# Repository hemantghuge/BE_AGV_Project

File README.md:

# BE_AGV_Project 2019-2020

## Project Title
Smart and Efficient Techniques for Automated Guided Vehicle

## College
Government College of Engineering and Research, Avasari (Khurd)

## Department
Electronics and Telecommunication Engineering

#### Click below for viewing YouTube video.

## Mentor

**Name:** Dr. Kirti Vasant Thakur
**Email ID:** kirti79@gmail.com

## Members

**Roll No.**: 16131002 **Name:** Aadesh Rambhau Borate **Email ID:** aadeshborate5@gmail.com

**Roll No.:** 16131035 **Name:** Hemant Goraksh Ghuge **Email ID:** hemantgghuge@gmail.com

**Roll No.:** 16131052 **Name:** Unnati Raju Kulkarni **Email ID:** unnatikulkarni46@gmail.com

**Roll No.:** 17231025 **Name:** Revati Anand Kulkarni **Email ID:** kulkarnirevati988@gmail.com

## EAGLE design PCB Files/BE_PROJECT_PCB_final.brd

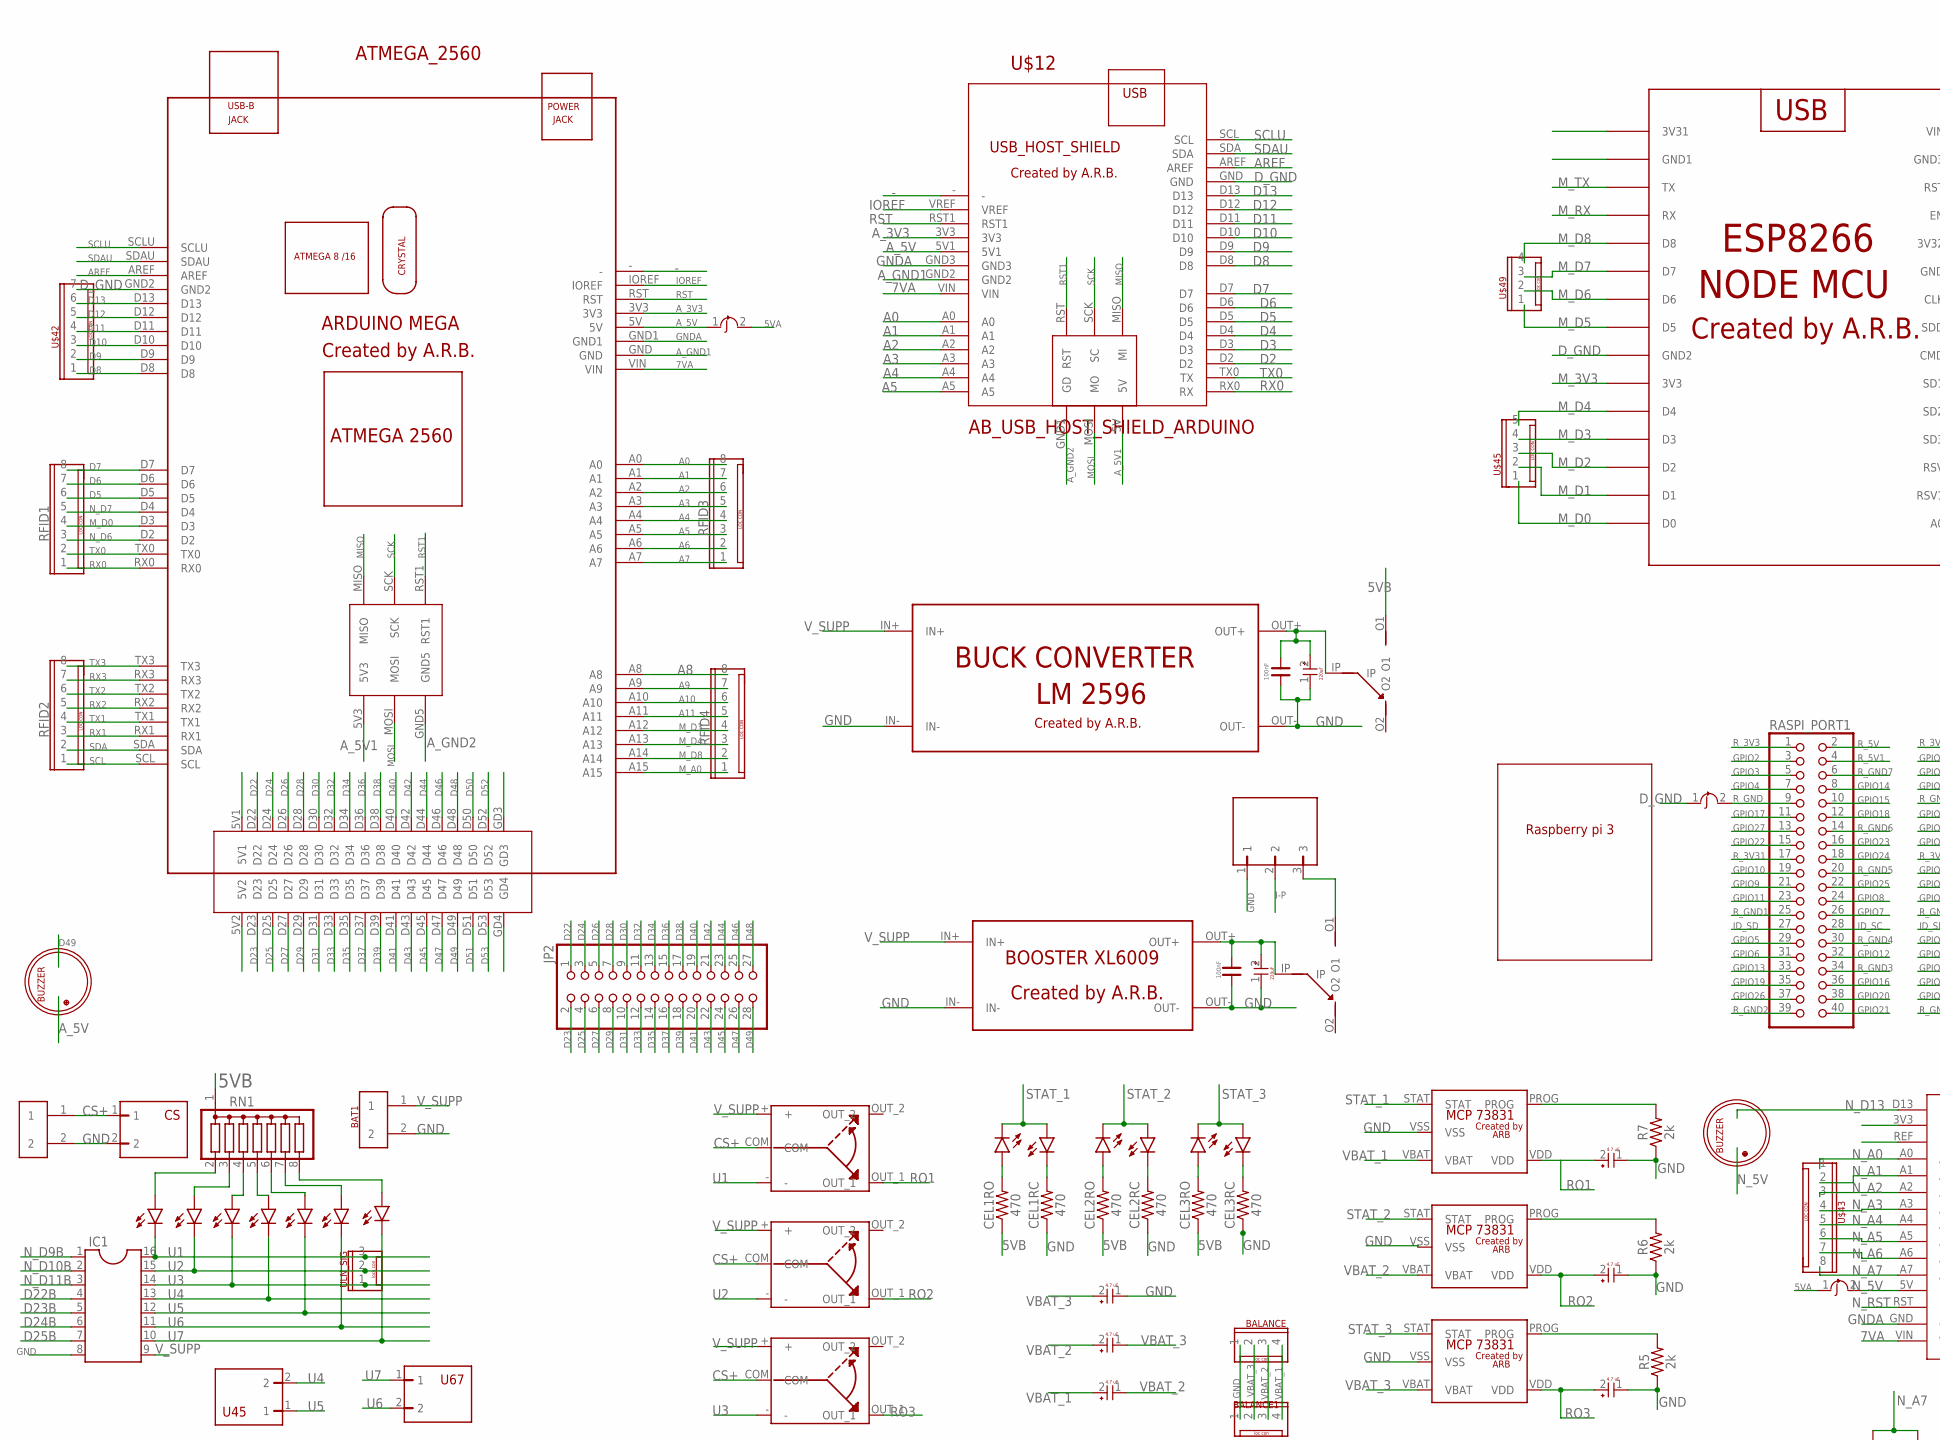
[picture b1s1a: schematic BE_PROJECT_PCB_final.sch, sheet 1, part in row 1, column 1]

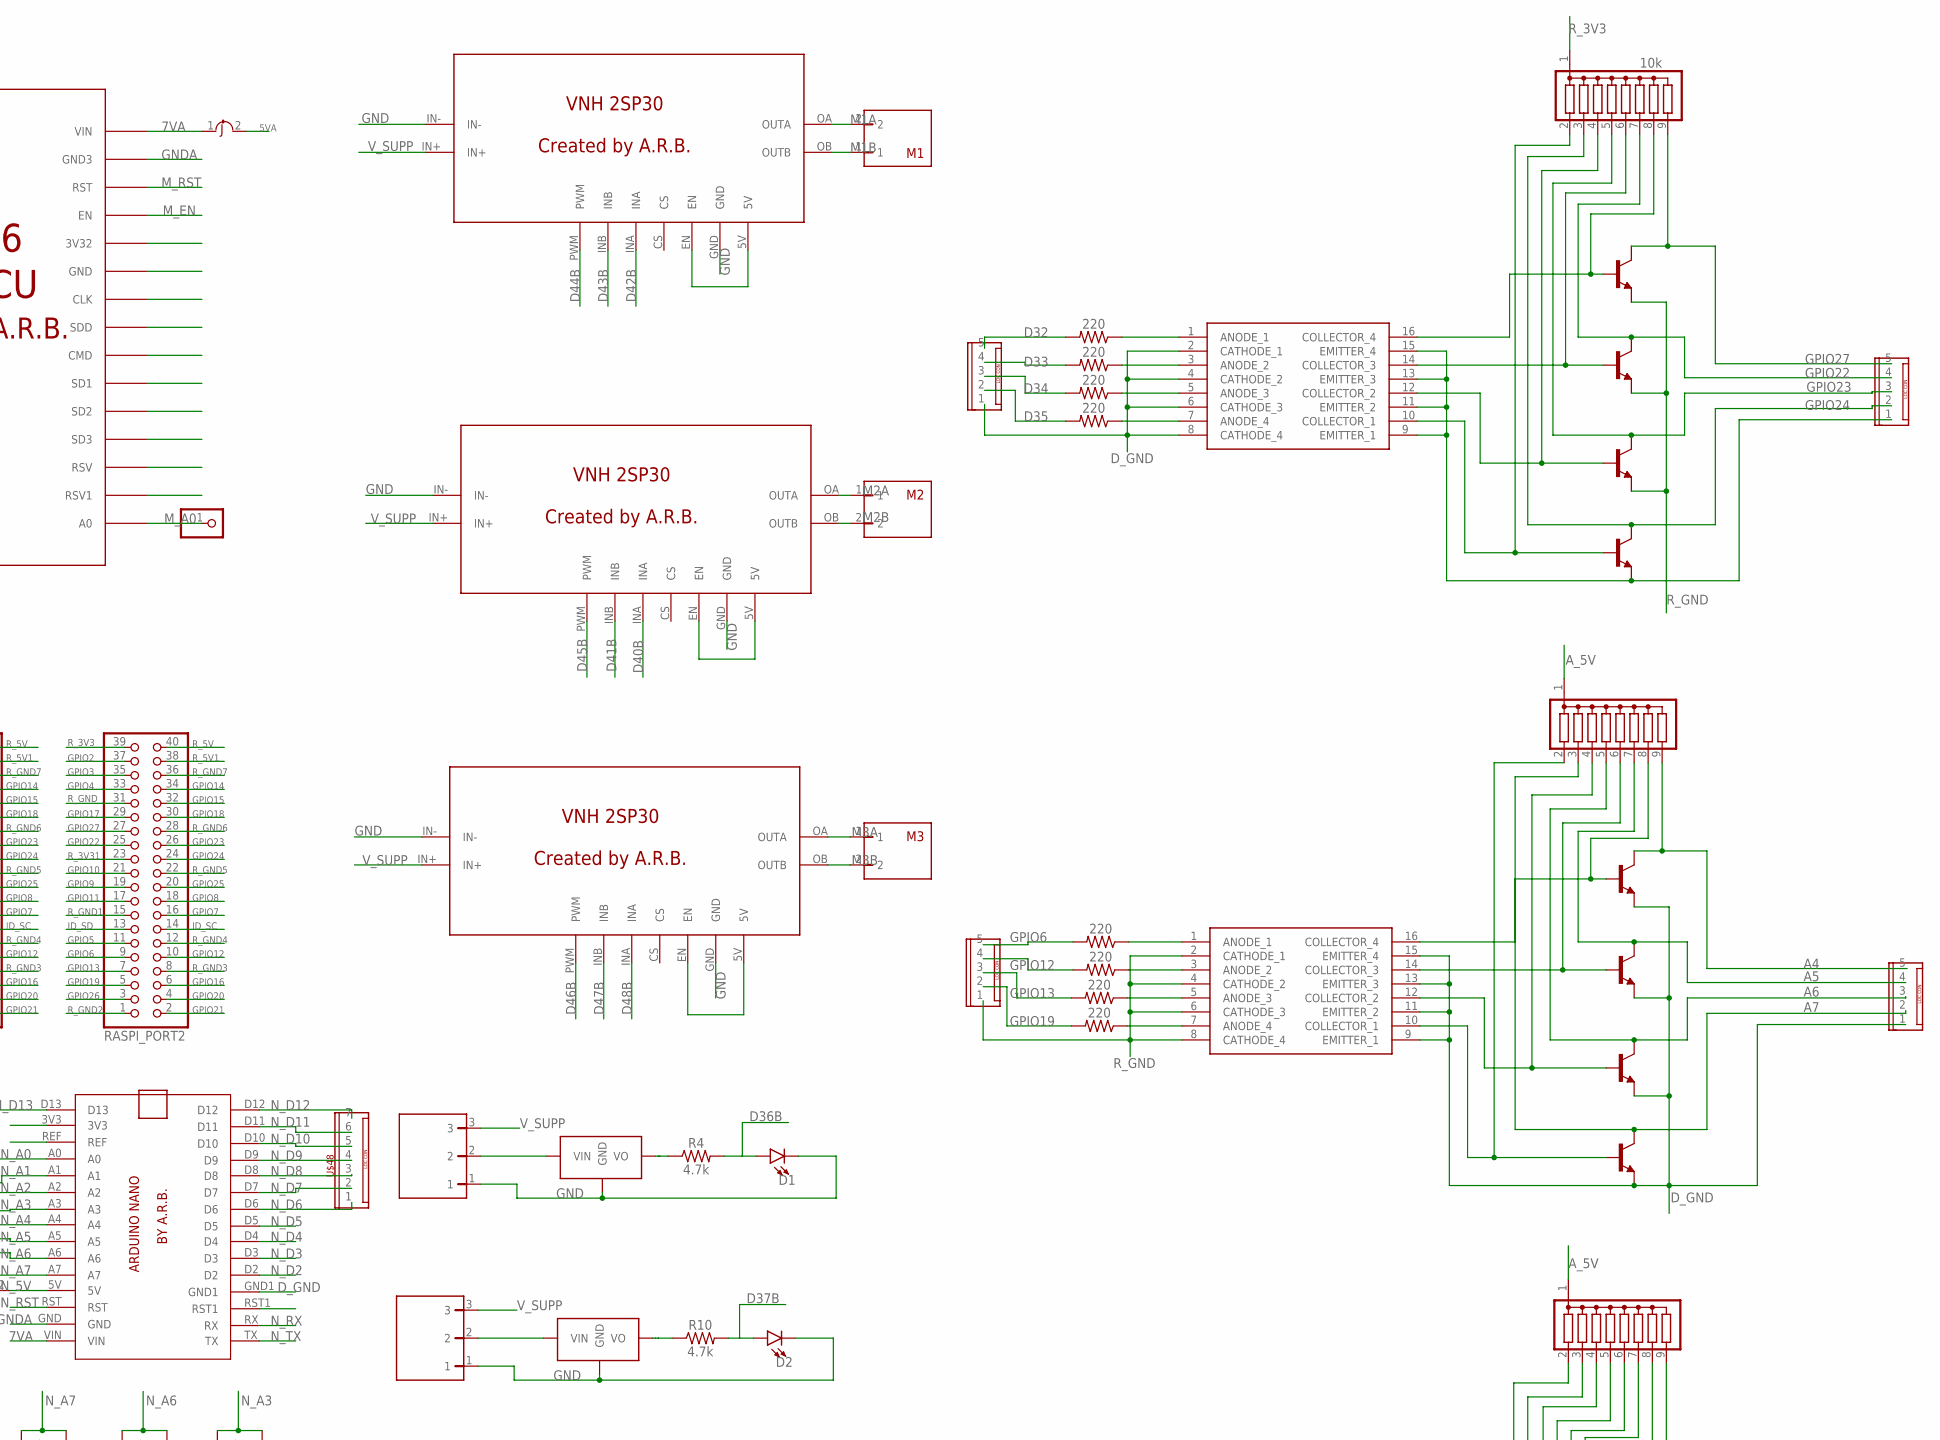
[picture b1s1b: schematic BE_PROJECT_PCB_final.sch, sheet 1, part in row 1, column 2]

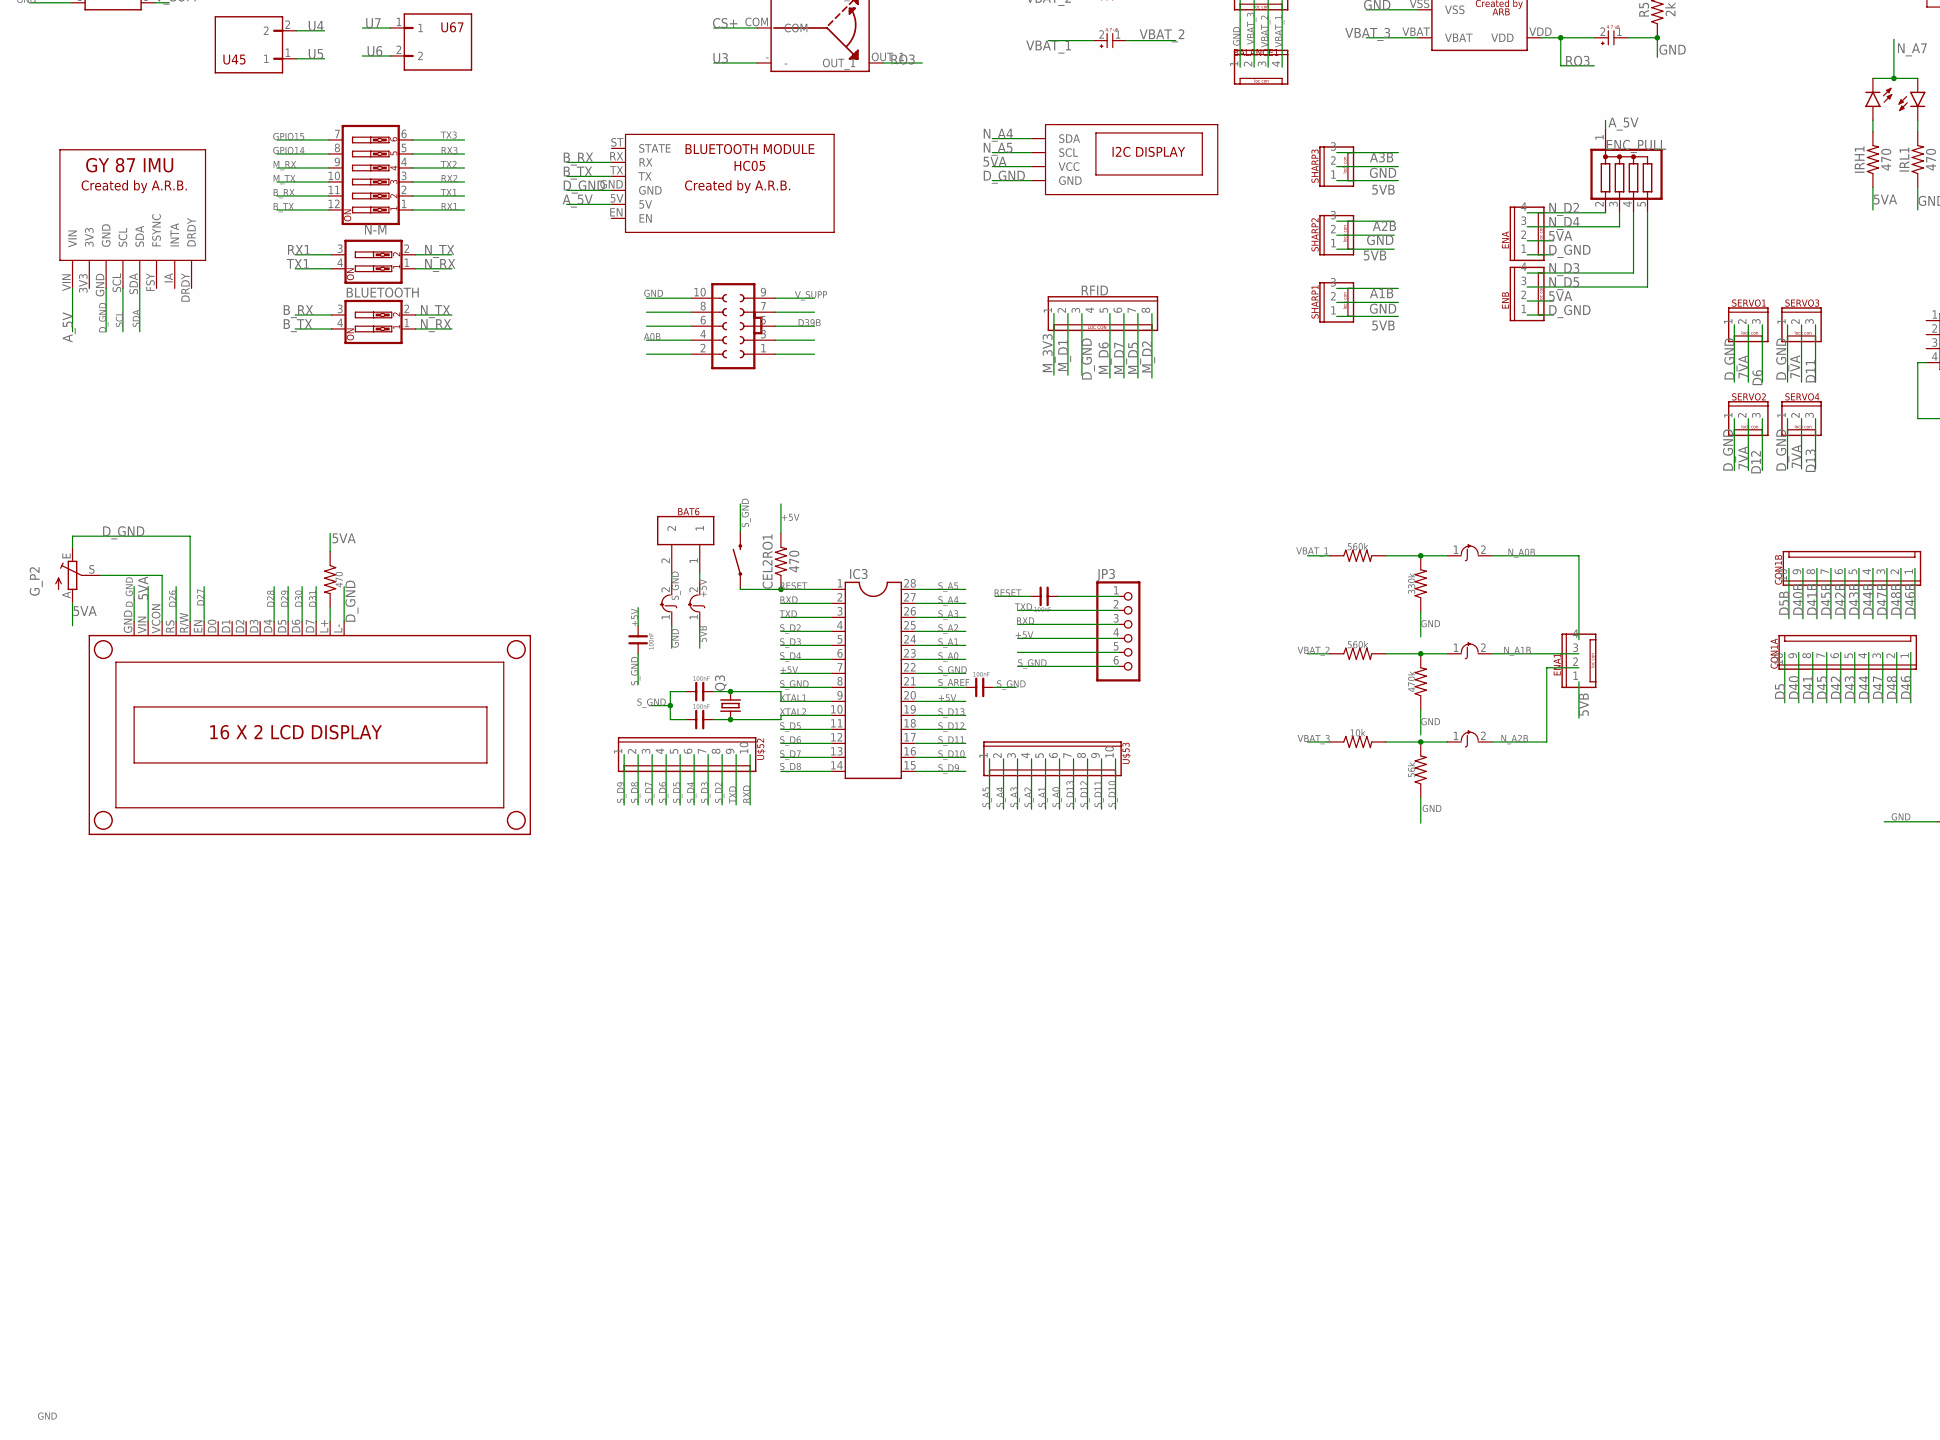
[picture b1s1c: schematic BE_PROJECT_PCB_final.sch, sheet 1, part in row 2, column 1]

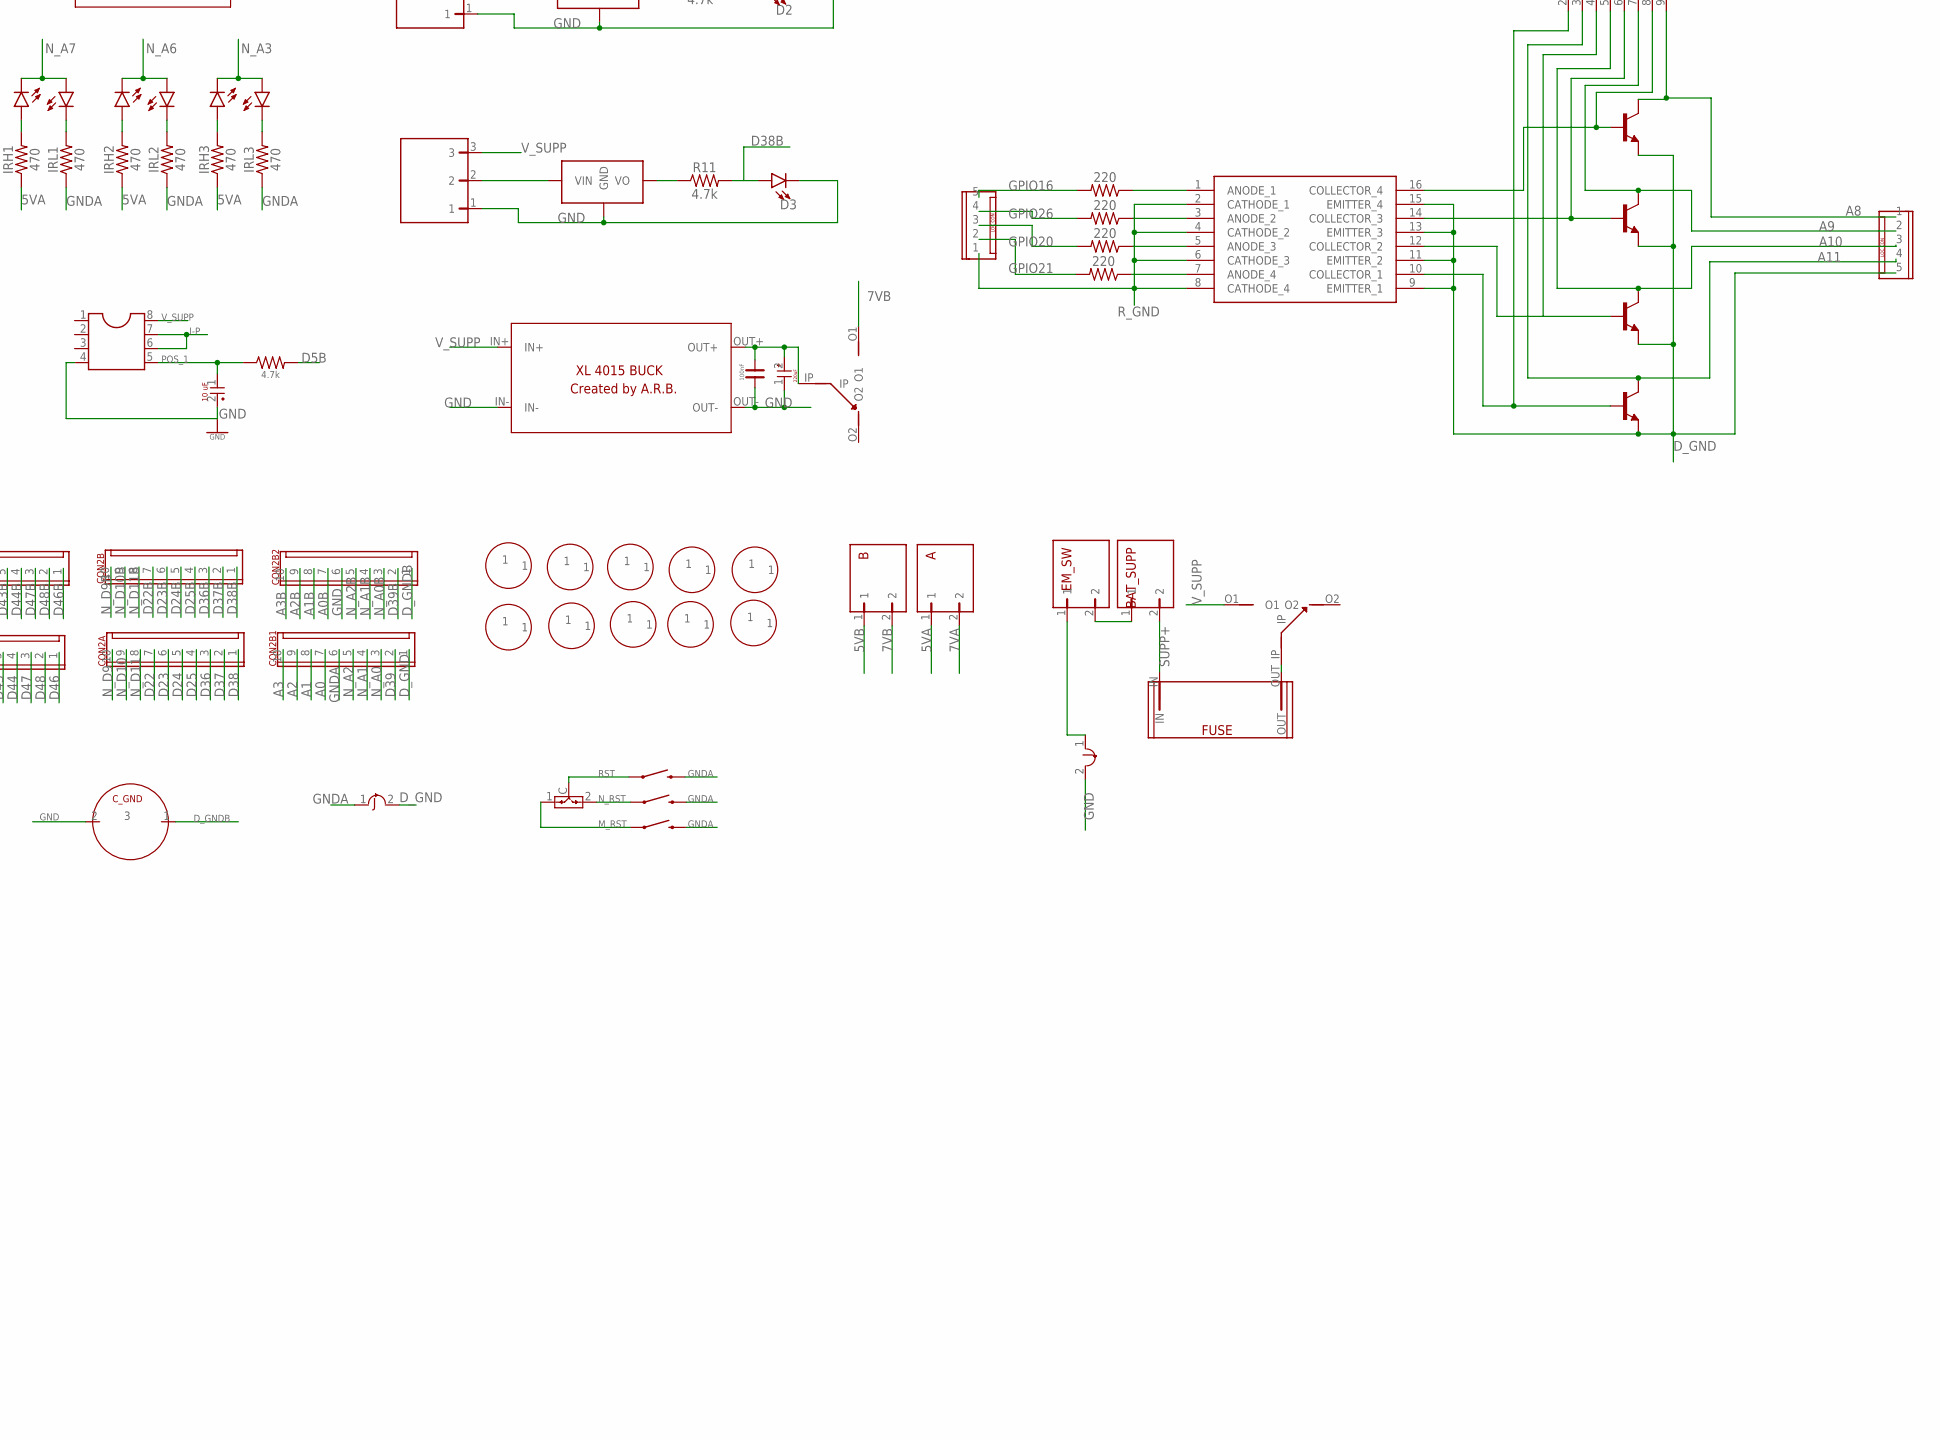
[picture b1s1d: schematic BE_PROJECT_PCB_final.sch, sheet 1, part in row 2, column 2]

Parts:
10K: 10k; SIL9
A: AB_RIGHT_TER_BLK
ATMEGA_2560: AB_ARDUINO_MEGA
B: AB_RIGHT_TER_BLK
BALANCE, BALANCE1: AB_4PIN_LOC_CONNECTOR
BAT1, BAT6: AB_SCREW_TERMINAL_5MM_2PIN
BAT_SUPP: AB_RIGHT_TER_BLK
BC547: BC547; TO92
BLUETOOTH: SW_DIP-2; EDG-02
C1, C2, C3, C4, C5, C6, C7, C8: 100nF; C020-035X018
CEL1CC, CEL1CO, CEL2CC, CEL2CO, CEL3CC, CEL3CO: LED-3MM-NO_SILK; LED_3MM-NS
CEL1RC, CEL1RO, CEL2RC, CEL2RO, CEL2RO1, CEL3RC, CEL3RO: 470; AXIAL-0.3
CON1A, CON1B, CON2A, CON2B, CON2B1, CON2B2: AB_10PIN_LOC_CONNECTOR
CS: AB_RIGHT_TER_BLK
C_GND: AB_JOINT_GND
D1, D2, D3: LED-3MM-NO_SILK; LED_3MM-NS
EM_SW: AB_RIGHT_TER_BLK
ENA, ENA1: AB_4PIN_LOC_CONNECTOR
ENB: AB_4PIN_LOC_CONNECTOR
ENC_PULL: G04R; SIL5
FUSE: AB_FUSE_HOLDER
G_P2: TRIM_EU-RS3; RS3
IC1: DIL16S; SOCKET-16
IC2: DIL8S; SOCKET-08
IC3: DIL28-3
IC8, IC9, IC10: TLP281-4(GB,J,F); SOIC127P700X210-16N
IH1, IH2, IH3: LED-3MM-NO_SILK; LED_3MM-NS
IL1, IL2, IL3: LED-3MM-NO_SILK; LED_3MM-NS
IRH1, IRH2, IRH3: 470; AXIAL-0.3
IRL1, IRL2, IRL3: 470; AXIAL-0.3
JP1: PINHD-1X1; 1X01
JP2: PINHD-2X14; 2X14
JP3: PINHD-1X6; 1X06
L1, L2, L3, L4, L5, L6, L7: LED-3MM-NO_SILK; LED_3MM-NS
LSA_2: LSA1; S10V
M1, M2, M3: AB_RIGHT_TER_BLK
MEGA_RST, MEGA_RST1: MOMENTARY-SWITCH-SPST-PTH-6.0MM; TACTILE_SWITCH_PTH_6.0MM
M_RST: MOMENTARY-SWITCH-SPST-PTH-6.0MM; TACTILE_SWITCH_PTH_6.0MM
N-M: SW_DIP-2; EDG-02
NANO: AB_JUMPER_ONE_WAY
NODEMCU: AB_JUMPER_ONE_WAY
N_RST: MOMENTARY-SWITCH-SPST-PTH-6.0MM; TACTILE_SWITCH_PTH_6.0MM
OISO1, OISO2, OISO3, OISO4, OISO5, OISO6: AB_5PIN_LOC_CONNECTOR
PPR_R1: 4.7k; AXIAL-0.3
PROX1, PROX2, PROX3: AB_RIGHT_TER_BLK_3PIN
Q3: CRYSTALHC49U-V; HC49U-V
R2, R35: 560k; AXIAL-0.3
R4, R10, R11: 4.7k; AXIAL-0.3
R5, R6, R7: 2k; AXIAL-0.3
R17: 470; AXIAL-0.3
R18, R19, R20, R21, R22, R23, R24, R25, R26, R27, R28, R32: 220; AXIAL-0.3
R34: 330k; AXIAL-0.3
R36: 470k; AXIAL-0.3
R37: 10k; AXIAL-0.3
R38: 56k; AXIAL-0.3
RASPI_PORT1, RASPI_PORT2: PINHD-2X20; 2X20
REL1, REL2, REL3: 12v; AB_ELECTROMAGNETIC_RELAY
RFID, RFID1, RFID2, RFID3, RFID4: AB_8PIN_LOC_CONNECTOR
RN1: G07R; SIL8
RN6, RN7: G08R; SIL9
SERVO1, SERVO2, SERVO3, SERVO4: AB_3PIN_LOC_CONNECTOR
SHARP1, SHARP2, SHARP3: AB_3PIN_LOC_CONNECTOR
SW1: SW_DIP-6; EDG-06
TR14, TR15, TR16, TR17, TR18, TR19, TR20, TR21, TR22, TR23, TR24: BC547; TO92
U45, U67: AB_RIGHT_TER_BLK
U$1, U$17, U$31, U$33, U$40, U$41, U$50, U$51, U$62: AB_JUMPER_ONE_WAY
U$2: AB_16X2_LCD_DISPLAY
U$3, U$6, U$9: AB_VNH2SP30; AB_VNH2SP30_MODULE
U$4: ESP8266_NODEMCU_BY_AB; AB_ESP8266_BREAKOUT
U$5: AB_RASPBERRY_PI_3
U$7: AB_LM2596_BUCK_CONVERTER
U$8: AB_XL6009_BOOST_CONVERTER; AB_XL6009E1_BOOST_CONVERTER
U$10: AB_GY87; AB_IMU_GY87
U$11: AB_BLUETOOTH_HC05
U$12: AB_USB_HOST_SHIELD_ARDUINO
U$13: AB_XL4015_5A_; AB_XL_4015_5A_BUCK
U$14, U$15, U$16, U$32: AB_SW
U$18, U$19, U$20: AB_MCP_73831_LIPO_CHARGER
U$21, U$22, U$23, U$25, U$26, U$27: 4.7 uF; AB_POL_CAP
U$24: AB_0.91_INCH_I2C_DISPLAY; AB_0.91INCH_I2C_DISPLAY
U$28, U$39: AB_BUZZER
U$29: 10 uF; AB_POL_CAP
U$30: AB_JUMPER_TWO_WAY
U$34, U$37, U$38: 220uF; AB_POL_CAP
U$35: AB_ARDUINO_NANO
U$36: AB_SCREW_TERMINAL_5MM_2PIN
U$42, U$48: AB_7PIN_LOC_CONNECTOR
U$43: AB_8PIN_LOC_CONNECTOR
U$44, U$46, U$47: AB_7805_FLAT
U$45: AB_5PIN_LOC_CONNECTOR
U$49: AB_4PIN_LOC_CONNECTOR
U$52, U$53: AB_10PIN_LOC_CONNECTOR
U$54, U$55, U$56, U$57, U$58, U$59, U$60, U$61, U$63, U$64: AB_PLATED_DRILL_160MIL
ULN_SIG: AB_3PIN_LOC_CONNECTOR
V-P: AB_RIGHT_TER_BLK_3PIN

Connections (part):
5VA: A.1, ENA.2, ENB.2, G_P2.A, IRH1.P$1 (1), IRH2.P$1 (1), IRH3.P$1 (1), NANO.1, NODEMCU.2, R17.P$1 (1), U$2.VIN, U$24.VCC, U$31.2
5VB: B.1, CEL1RO.P$1 (1), CEL2RO.P$1 (1), CEL3RO.P$1 (1), ENA1.1, RN1.1, SHARP1.1, SHARP2.1, SHARP3.1, U$14.O1, U$50.1
7VA: A.2, ATMEGA_2560.VIN, NODEMCU.1, SERVO1.2, SERVO2.2, SERVO3.2, SERVO4.2, U$4.VIN, U$12.VIN, U$35.VIN
7VB: B.2, U$16.O1
+5V: BAT6.1, C5.1, CEL2RO1.P$2 (2), IC3.7, IC3.20, JP3.4, U$50.2
-: ATMEGA_2560.-, U$12.-
A0: ATMEGA_2560.A0, CON2B1.7, RFID3.8, U$12.A0
A0B: CON2B2.7, LSA_2.4
A1: ATMEGA_2560.A1, CON2B1.8, RFID3.7, U$12.A1
A1B: CON2B2.8, SHARP1.3
A2: ATMEGA_2560.A2, CON2B1.9, RFID3.6, U$12.A2
A2B: CON2B2.9, SHARP2.3
A3: ATMEGA_2560.A3, CON2B1.10, RFID3.5, U$12.A3
A3B: CON2B2.10, SHARP3.3
A4: ATMEGA_2560.A4, OISO4.5, RFID3.4, RN6.9, TR17.3 (C), U$12.A4
A5: ATMEGA_2560.A5, OISO4.4, RFID3.3, RN6.7, TR18.3 (C), U$12.A5
A6: ATMEGA_2560.A6, OISO4.3, RFID3.2, RN6.5, TR19.3 (C)
A7: ATMEGA_2560.A7, OISO4.2, RFID3.1, RN6.3, TR20.3 (C)
A8: ATMEGA_2560.A8, OISO6.1, RFID4.8, RN7.9, TR21.3 (C)
A9: ATMEGA_2560.A9, OISO6.2, RFID4.7, RN7.7, TR22.3 (C)
A10: ATMEGA_2560.A10, OISO6.3, RFID4.6, RN7.5, TR23.3 (C)
A11: ATMEGA_2560.A11, OISO6.4, RFID4.5, RN7.3, TR24.3 (C)
AREF: ATMEGA_2560.AREF, U$12.AREF
A_3V3: ATMEGA_2560.3V3, U$12.3V3
A_5V: ATMEGA_2560.5V, ENC_PULL.1, RN6.1, RN7.1, U$10.VIN, U$11.5V, U$12.5V1, U$31.1, U$39.+
A_5V1: ATMEGA_2560.5V3, U$12.5V
A_GND1: ATMEGA_2560.GND, U$12.GND2
A_GND2: ATMEGA_2560.GND5, U$12.GND1 (GD)
B_RX: BLUETOOTH.3, SW1.11, U$11.RX
B_TX: BLUETOOTH.4, SW1.12, U$11.TX
CS+: CS.1, REL1.COM, REL2.COM, REL3.COM, U$36.1
D2: U$12.D2
D3: U$12.D3
D4: U$12.D4
D5: ATMEGA_2560.D5, CON1A.10, RFID1.6, U$12.D5
D5B: CON1B.10, PPR_R1.P$2 (2)
D6: ATMEGA_2560.D6, RFID1.7, SERVO1.3, U$12.D6
D7: ATMEGA_2560.D7, RFID1.8, U$12.D7
D8: ATMEGA_2560.D8, U$12.D8, U$42.1
D9: ATMEGA_2560.D9, U$12.D9, U$42.2
D10: ATMEGA_2560.D10, U$12.D10, U$42.3
D11: ATMEGA_2560.D11, SERVO3.3, U$12.D11, U$42.4
D12: ATMEGA_2560.D12, SERVO2.3, U$12.D12, U$42.5
D13: ATMEGA_2560.D13, SERVO4.3, U$12.D13, U$42.6
D22: ATMEGA_2560.D22, CON2A.7, JP2.1
D22B: CON2B.7, IC1.4
D23: ATMEGA_2560.D23, CON2A.6, JP2.2
D23B: CON2B.6, IC1.5
D24: ATMEGA_2560.D24, CON2A.5, JP2.3
D24B: CON2B.5, IC1.6
D25: ATMEGA_2560.D25, CON2A.4, JP2.4
D25B: CON2B.4, IC1.7
D26: ATMEGA_2560.D26, JP2.5, U$2.RS
D27: ATMEGA_2560.D27, JP2.6, U$2.EN
D28: ATMEGA_2560.D28, JP2.7, U$2.D4
D29: ATMEGA_2560.D29, JP2.8, U$2.D5
D30: ATMEGA_2560.D30, JP2.9, U$2.D6
D31: ATMEGA_2560.D31, JP2.10, U$2.D7
D32: ATMEGA_2560.D32, JP2.11, OISO1.5, R32.P$2 (2)
D33: ATMEGA_2560.D33, JP2.12, OISO1.4, R18.P$2 (2)
D34: ATMEGA_2560.D34, JP2.13, OISO1.3, R19.P$2 (2)
D35: ATMEGA_2560.D35, JP2.14, OISO1.2, R20.P$2 (2)
D36: ATMEGA_2560.D36, CON2A.3, JP2.15
D36B: CON2B.3, D1.A, R4.P$2 (2)
D37: ATMEGA_2560.D37, CON2A.2, JP2.16
D37B: CON2B.2, D2.A, R10.P$2 (2)
D38: ATMEGA_2560.D38, CON2A.1, JP2.17
D38B: CON2B.1, D3.A, R11.P$2 (2)
D39: ATMEGA_2560.D39, CON2B1.2, JP2.18
D39B: CON2B2.2, LSA_2.5
D40: ATMEGA_2560.D40, CON1A.9, JP2.19
D40B: CON1B.9, U$6.INA
D41: ATMEGA_2560.D41, CON1A.8, JP2.20
D41B: CON1B.8, U$6.INB
D42: ATMEGA_2560.D42, CON1A.6, JP2.21
D42B: CON1B.6, U$3.INA
D43: ATMEGA_2560.D43, CON1A.5, JP2.22
D43B: CON1B.5, U$3.INB
D44: ATMEGA_2560.D44, CON1A.4, JP2.23
D44B: CON1B.4, U$3.PWM
D45: ATMEGA_2560.D45, CON1A.7, JP2.24
D45B: CON1B.7, U$6.PWM
D46: ATMEGA_2560.D46, CON1A.1, JP2.25
D46B: CON1B.1, U$9.PWM
D47: ATMEGA_2560.D47, CON1A.3, JP2.26
D47B: CON1B.3, U$9.INB
D48: ATMEGA_2560.D48, CON1A.2, JP2.27
D48B: CON1B.2, U$9.INA
D49: ATMEGA_2560.D49, JP2.28, U$39.-
D50: ATMEGA_2560.D50
D51: ATMEGA_2560.D51
D52: ATMEGA_2560.D52
D53: ATMEGA_2560.D53
D_GND: ATMEGA_2560.GND2, CON2B1.1, ENA.1, ENB.1, G_P2.E, IC8.2 (CATHODE_1), IC8.4 (CATHODE_2), IC8.6 (CATHODE_3), IC8.8 (CATHODE_4), IC9.9 (EMITTER_1), IC9.11 (EMITTER_2), IC9.13 (EMITTER_3), IC9.15 (EMITTER_4), IC10.9 (EMITTER_1), IC10.11 (EMITTER_2), IC10.13 (EMITTER_3), IC10.15 (EMITTER_4), OISO1.1, OISO4.1, OISO6.5, RFID.3, SERVO1.1, SERVO2.1, SERVO3.1, SERVO4.1, TR17.1 (E), TR18.1 (E), TR19.1 (E), TR20.1 (E), TR21.1 (E), TR22.1 (E), TR23.1 (E), TR24.1 (E), U$2.GND, U$2.L-, U$2.R/W, U$4.GND2, U$10.GND, U$11.GND, U$12.GND, U$17.1, U$24.GND, U$35.GND1, U$42.7, U$62.2
D_GNDB: CON2B2.1, C_GND.1
GND: BALANCE.1, BALANCE1.1, BAT1.2, C1.1, C3.1, C4.1, CEL1RC.P$1 (1), CEL2RC.P$1 (1), CEL3RC.P$1 (1), CON2B2.6, CS.2, C_GND.2, D1.K (C), D2.K (C), D3.K (C), IC1.8, IC2.4, LSA_2.10, PROX1.1, PROX2.1, PROX3.1, R5.P$1 (1), R6.P$1 (1), R7.P$1 (1), R34.P$1 (1), R36.P$1 (1), R38.P$1 (1), SHARP1.2, SHARP2.2, SHARP3.2, U$3.GND, U$3.IN-, U$6.GND, U$6.IN-, U$7.IN-, U$7.OUT-, U$8.IN-, U$8.OUT-, U$9.GND, U$9.IN-, U$13.IN-, U$13.OUT-, U$18.VSS, U$19.VSS, U$20.VSS, U$23.1, U$25.1, U$26.1, U$27.1, U$29.2, U$33.2, U$34.1, U$36.2, U$37.1, U$38.1, U$44.2 (GND), U$46.2 (GND), U$47.2 (GND), U$51.1, V-P.1
GNDA: ATMEGA_2560.GND1, CON2B1.6, IRL1.P$1 (1), IRL2.P$1 (1), IRL3.P$1 (1), MEGA_RST.3 (2), M_RST.3 (2), N_RST.3 (2), U$4.GND3, U$12.GND3, U$35.GND, U$62.1
GPIO2: RASPI_PORT1.3, RASPI_PORT2.37
GPIO3: RASPI_PORT1.5, RASPI_PORT2.35
GPIO4: RASPI_PORT1.7, RASPI_PORT2.33
GPIO5: RASPI_PORT1.29, RASPI_PORT2.11
GPIO6: OISO3.5, R21.P$2 (2), RASPI_PORT1.31, RASPI_PORT2.9
GPIO7: RASPI_PORT1.26, RASPI_PORT2.16
GPIO8: RASPI_PORT1.24, RASPI_PORT2.18
GPIO9: RASPI_PORT1.21, RASPI_PORT2.19
GPIO10: RASPI_PORT1.19, RASPI_PORT2.21
GPIO11: RASPI_PORT1.23, RASPI_PORT2.17
GPIO12: OISO3.4, R22.P$2 (2), RASPI_PORT1.32, RASPI_PORT2.10
GPIO13: OISO3.3, R23.P$2 (2), RASPI_PORT1.33, RASPI_PORT2.7
GPIO14: RASPI_PORT1.8, RASPI_PORT2.34, SW1.8
GPIO15: RASPI_PORT1.10, RASPI_PORT2.32, SW1.7
GPIO16: OISO5.5, R25.P$2 (2), RASPI_PORT1.36, RASPI_PORT2.6
GPIO17: RASPI_PORT1.11, RASPI_PORT2.29
GPIO18: RASPI_PORT1.12, RASPI_PORT2.30
GPIO19: OISO3.2, R24.P$2 (2), RASPI_PORT1.35, RASPI_PORT2.5
GPIO20: OISO5.3, R27.P$2 (2), RASPI_PORT1.38, RASPI_PORT2.4
GPIO21: OISO5.2, R28.P$2 (2), RASPI_PORT1.40, RASPI_PORT2.2
GPIO22: 10K.7, OISO2.4, RASPI_PORT1.15, RASPI_PORT2.25, TR14.3 (C)
GPIO23: 10K.5, OISO2.3, RASPI_PORT1.16, RASPI_PORT2.26, TR15.3 (C)
GPIO24: 10K.3, OISO2.2, RASPI_PORT1.18, RASPI_PORT2.24, TR16.3 (C)
GPIO25: RASPI_PORT1.22, RASPI_PORT2.20
GPIO26: OISO5.4, R26.P$2 (2), RASPI_PORT1.37, RASPI_PORT2.3
GPIO27: 10K.9, BC547.3 (C), OISO2.5, RASPI_PORT1.13, RASPI_PORT2.27
I-P: IC2.6, IC2.7, V-P.2
ID_SC: RASPI_PORT1.28, RASPI_PORT2.14
ID_SD: RASPI_PORT1.27, RASPI_PORT2.13
IOREF: ATMEGA_2560.IOREF, U$12.VREF
M1A: M1.2, U$3.OA (OUTA)
M1B: M1.1, U$3.OB (OUTB)
M2A: M2.1, U$6.OA (OUTA)
M2B: M2.2, U$6.OB (OUTB)
M3A: M3.1, U$9.OA (OUTA)
M3B: M3.2, U$9.OB (OUTB)
MISO: ATMEGA_2560.MISO, U$12.MISO (MI)
MOSI: ATMEGA_2560.MOSI, U$12.MOSI (MO)
M_3V3: RFID.1, U$4.3V3
M_A0: ATMEGA_2560.A15, JP1.1, RFID4.1, U$4.A0
M_D0: ATMEGA_2560.D3, RFID1.4, U$4.D0, U$45.1
M_D1: RFID.2, U$4.D1, U$45.2
M_D2: RFID.8, U$4.D2, U$45.3
M_D3: ATMEGA_2560.A12, RFID4.4, U$4.D3, U$45.4
M_D4: ATMEGA_2560.A13, RFID4.3, U$4.D4, U$45.5
M_D5: RFID.7, U$4.D5, U$49.1
M_D6: RFID.5, U$4.D6, U$49.2
M_D7: RFID.6, U$4.D7, U$49.3
M_D8: ATMEGA_2560.A14, RFID4.2, U$4.D8, U$49.4
M_EN: U$4.EN
M_RST: M_RST.1, U$4.RST, U$30.1
M_RX: SW1.9, U$4.RX
M_TX: SW1.10, U$4.TX
unnamed: C1.2, U$7.OUT+, U$14.IP, U$34.2
unnamed: IC10.7 (ANODE_4), R28.P$1 (1)
unnamed: IC9.7 (ANODE_4), R24.P$1 (1)
unnamed: U$15.O1, V-P.3
unnamed: G_P2.S, U$2.VCON
unnamed: PROX1.2, U$44.1 (VIN)
unnamed: R4.P$1 (1), U$44.3 (VO)
unnamed: PROX3.2, U$47.1 (VIN)
unnamed: 10K.4, IC8.12 (COLLECTOR_2), TR15.2 (B)
unnamed: IC9.16 (COLLECTOR_4), RN6.8, TR17.2 (B)
unnamed: R11.P$1 (1), U$47.3 (VO)
unnamed: R2.P$2 (2), R34.P$2 (2), U$1.1
unnamed: EM_SW.1, U$33.1
unnamed: 10K.2, IC8.10 (COLLECTOR_1), TR16.2 (B)
unnamed: 10K.8, BC547.2 (B), IC8.16 (COLLECTOR_4)
unnamed: FUSE.OUT, U$32.IP
unnamed: R35.P$2 (2), R36.P$2 (2), U$40.1
unnamed: IC9.10 (COLLECTOR_1), RN6.2, TR20.2 (B)
unnamed: R17.P$2 (2), U$2.L+
unnamed: U$3.5V, U$3.EN
unnamed: U$6.5V, U$6.EN
unnamed: 10K.6, IC8.14 (COLLECTOR_3), TR14.2 (B)
unnamed: C3.2, U$8.OUT+, U$15.IP, U$37.2
unnamed: R37.P$2 (2), R38.P$2 (2), U$41.1
unnamed: IC9.12 (COLLECTOR_2), RN6.4, TR19.2 (B)
unnamed: IC9.14 (COLLECTOR_3), RN6.6, TR18.2 (B)
unnamed: U$9.5V, U$9.EN
unnamed: C4.2, U$13.OUT+, U$16.IP, U$38.2
unnamed: IC10.10 (COLLECTOR_1), RN7.2, TR24.2 (B)
unnamed: IC10.12 (COLLECTOR_2), RN7.4, TR23.2 (B)
unnamed: IC10.14 (COLLECTOR_3), RN7.6, TR22.2 (B)
unnamed: IC10.16 (COLLECTOR_4), RN7.8, TR21.2 (B)
unnamed: CEL2CO.A, CEL2RO.P$2 (2)
unnamed: IH3.A, IRH3.P$2 (2)
unnamed: CEL3CO.A, CEL3RO.P$2 (2)
unnamed: CEL3CC.K (C), CEL3RC.P$2 (2)
unnamed: CEL2CC.K (C), CEL2RC.P$2 (2)
unnamed: CEL1CO.A, CEL1RO.P$2 (2)
unnamed: CEL1CC.K (C), CEL1RC.P$2 (2)
unnamed: IL3.K (C), IRL3.P$2 (2)
unnamed: IH2.A, IRH2.P$2 (2)
unnamed: IL2.K (C), IRL2.P$2 (2)
unnamed: R7.P$2 (2), U$18.PROG
unnamed: IH1.A, IRH1.P$2 (2)
unnamed: R6.P$2 (2), U$19.PROG
unnamed: IL1.K (C), IRL1.P$2 (2)
unnamed: R5.P$2 (2), U$20.PROG
unnamed: C2.1, JP3.1
unnamed: L1.A, RN1.2
unnamed: L2.A, RN1.3
unnamed: L3.A, RN1.4
unnamed: L4.A, RN1.5
unnamed: L5.A, RN1.6
unnamed: L6.A, RN1.7
unnamed: L7.A, RN1.8
unnamed: PROX2.2, U$46.1 (VIN)
unnamed: R10.P$1 (1), U$46.3 (VO)
unnamed: IC8.1 (ANODE_1), R32.P$1 (1)
unnamed: IC8.3 (ANODE_2), R18.P$1 (1)
unnamed: IC8.5 (ANODE_3), R19.P$1 (1)
unnamed: IC8.7 (ANODE_4), R20.P$1 (1)
unnamed: IC9.1 (ANODE_1), R21.P$1 (1)
unnamed: IC9.3 (ANODE_2), R22.P$1 (1)
unnamed: IC9.5 (ANODE_3), R23.P$1 (1)
unnamed: IC10.1 (ANODE_1), R25.P$1 (1)
unnamed: IC10.3 (ANODE_2), R26.P$1 (1)
unnamed: IC10.5 (ANODE_3), R27.P$1 (1)
N_5V: NANO.2, U$28.+, U$35.5V
N_A0: CON2B1.3, U$35.A0, U$43.1
N_A0B: CON2B2.3, ENA1.4, U$1.2
N_A1: CON2B1.4, U$35.A1, U$43.2
N_A1B: CON2B2.4, ENA1.3, U$40.2
N_A2: CON2B1.5, U$35.A2, U$43.3
N_A2B: CON2B2.5, ENA1.2, U$41.2
N_A3: IH3.K (C), IL3.A, U$35.A3, U$43.4
N_A4: U$24.SDA, U$35.A4, U$43.5
N_A5: U$24.SCL, U$35.A5, U$43.6
N_A6: IH2.K (C), IL2.A, U$35.A6, U$43.7
N_A7: IH1.K (C), IL1.A, U$35.A7, U$43.8
N_D2: ENA.4, ENC_PULL.2, U$35.D2
N_D3: ENB.4, ENC_PULL.4, U$35.D3
N_D4: ENA.3, ENC_PULL.3, U$35.D4
N_D5: ENB.3, ENC_PULL.5, U$35.D5
N_D6: ATMEGA_2560.D2, RFID1.3, U$35.D6, U$48.1
N_D7: ATMEGA_2560.D4, RFID1.5, U$35.D7, U$48.2
N_D8: U$35.D8, U$48.3
N_D9: CON2A.10, U$35.D9, U$48.4
N_D9B: CON2B.10, IC1.1
N_D10: CON2A.9, U$35.D10, U$48.5
N_D10B: CON2B.9, IC1.2
N_D11: CON2A.8, U$35.D11, U$48.6
N_D11B: CON2B.8, IC1.3
N_D12: U$35.D12, U$48.7
N_D13: U$28.-, U$35.D13
N_RST: N_RST.1, U$30.2, U$35.RST
N_RX: BLUETOOTH.1, N-M.1, U$35.RX
N_TX: BLUETOOTH.2, N-M.2, U$35.TX
POS_1: IC2.5, PPR_R1.P$1 (1), U$29.1
RESET: C2.2, CEL2RO1.P$1 (1), IC3.1, MEGA_RST1.1
RO1: REL1.OUT_1, U$18.VDD, U$25.2
RO2: REL2.OUT_1, U$19.VDD, U$26.2
RO3: REL3.OUT_1, U$20.VDD, U$27.2
RST: ATMEGA_2560.RST, MEGA_RST.1, U$12.RST1, U$30.C
RST1: ATMEGA_2560.RST1, U$12.RST
RX0: ATMEGA_2560.RX0, RFID1.1, U$12.RX0 (RX)
RX1: ATMEGA_2560.RX1, N-M.3, RFID2.3, SW1.1
RX2: ATMEGA_2560.RX2, RFID2.5, SW1.3
RX3: ATMEGA_2560.RX3, RFID2.7, SW1.5
RXD: IC3.2, JP3.3, U$52.10
R_3V3: 10K.1, RASPI_PORT1.1, RASPI_PORT2.39
R_3V31: RASPI_PORT1.17, RASPI_PORT2.23
R_5V: RASPI_PORT1.2, RASPI_PORT2.40
R_5V1: RASPI_PORT1.4, RASPI_PORT2.38
R_GND: BC547.1 (E), IC8.9 (EMITTER_1), IC8.11 (EMITTER_2), IC8.13 (EMITTER_3), IC8.15 (EMITTER_4), IC9.2 (CATHODE_1), IC9.4 (CATHODE_2), IC9.6 (CATHODE_3), IC9.8 (CATHODE_4), IC10.2 (CATHODE_1), IC10.4 (CATHODE_2), IC10.6 (CATHODE_3), IC10.8 (CATHODE_4), OISO2.1, OISO3.1, OISO5.1, RASPI_PORT1.9, RASPI_PORT2.31, TR14.1 (E), TR15.1 (E), TR16.1 (E), U$17.2
R_GND1: RASPI_PORT1.25, RASPI_PORT2.15
R_GND2: RASPI_PORT1.39, RASPI_PORT2.1
R_GND3: RASPI_PORT1.34, RASPI_PORT2.8
R_GND4: RASPI_PORT1.30, RASPI_PORT2.12
R_GND5: RASPI_PORT1.20, RASPI_PORT2.22
R_GND6: RASPI_PORT1.14, RASPI_PORT2.28
R_GND7: RASPI_PORT1.6, RASPI_PORT2.36
SCK: ATMEGA_2560.SCK, U$12.SCK (SC)
SCL: ATMEGA_2560.SCL, RFID2.1, U$10.SCL
SCLU: ATMEGA_2560.SCLU, U$12.SCL
SDA: ATMEGA_2560.SDA, RFID2.2, U$10.SDA
SDAU: ATMEGA_2560.SDAU, U$12.SDA
STAT_1: CEL1CC.A, CEL1CO.K (C), U$18.STAT
STAT_2: CEL2CC.A, CEL2CO.K (C), U$19.STAT
STAT_3: CEL3CC.A, CEL3CO.K (C), U$20.STAT
SUPP+: BAT_SUPP.2, FUSE.IN
S_A0: IC3.23, U$53.6
S_A1: IC3.24, U$53.5
S_A2: IC3.25, U$53.4
S_A3: IC3.26, U$53.3
S_A4: IC3.27, U$53.2
S_A5: IC3.28, U$53.1
S_AREF: C8.1, IC3.21
S_D2: IC3.4, U$52.8
S_D3: IC3.5, U$52.7
S_D4: IC3.6, U$52.6
S_D5: IC3.11, U$52.5
S_D6: IC3.12, U$52.4
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
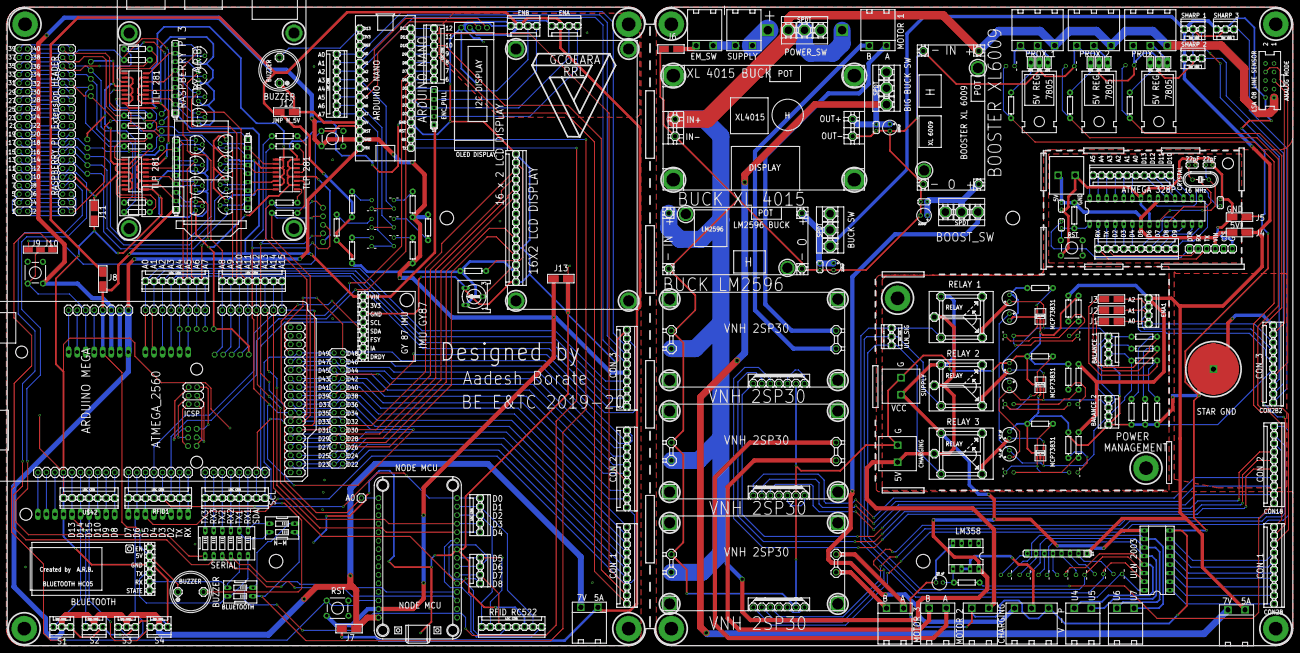
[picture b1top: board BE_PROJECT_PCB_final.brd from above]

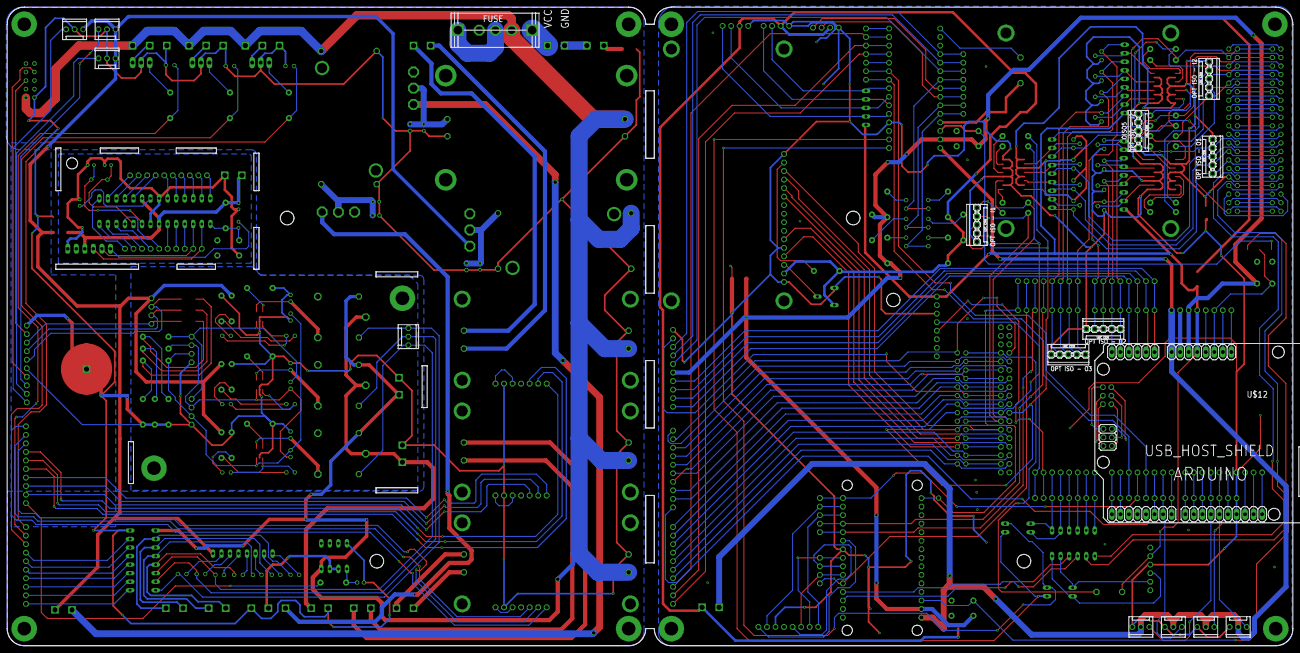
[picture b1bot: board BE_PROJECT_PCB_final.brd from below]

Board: 2 copper layers, 382.5 x 190.0 mm, 225 parts (8 on the bottom side), 311 nets.

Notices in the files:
parts and their libraries:
SparkFun-Resistors: Licensing: Creative Commons ShareAlike 4.0 International - https://creativecommons.org/licenses/by-sa/4.0
